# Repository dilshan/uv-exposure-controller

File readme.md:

## ATTiny2313 base electronic controller for UV exposure units.

*ATtiny2313A* MCU base exposure controller unit with two high-power relay driver stages, an audible notification unit, a safety lock, and a programmable timer. The programmable timer unit supports up to 999 seconds (approximately 16 minutes) of exposure.

This unit tests with four *NEC* 20W - 60cm (T8) black fluorescent tubes with four separate chokes and starter units.

The unit is specifically designed for developing screens (for screen-printing) and for paint curing.

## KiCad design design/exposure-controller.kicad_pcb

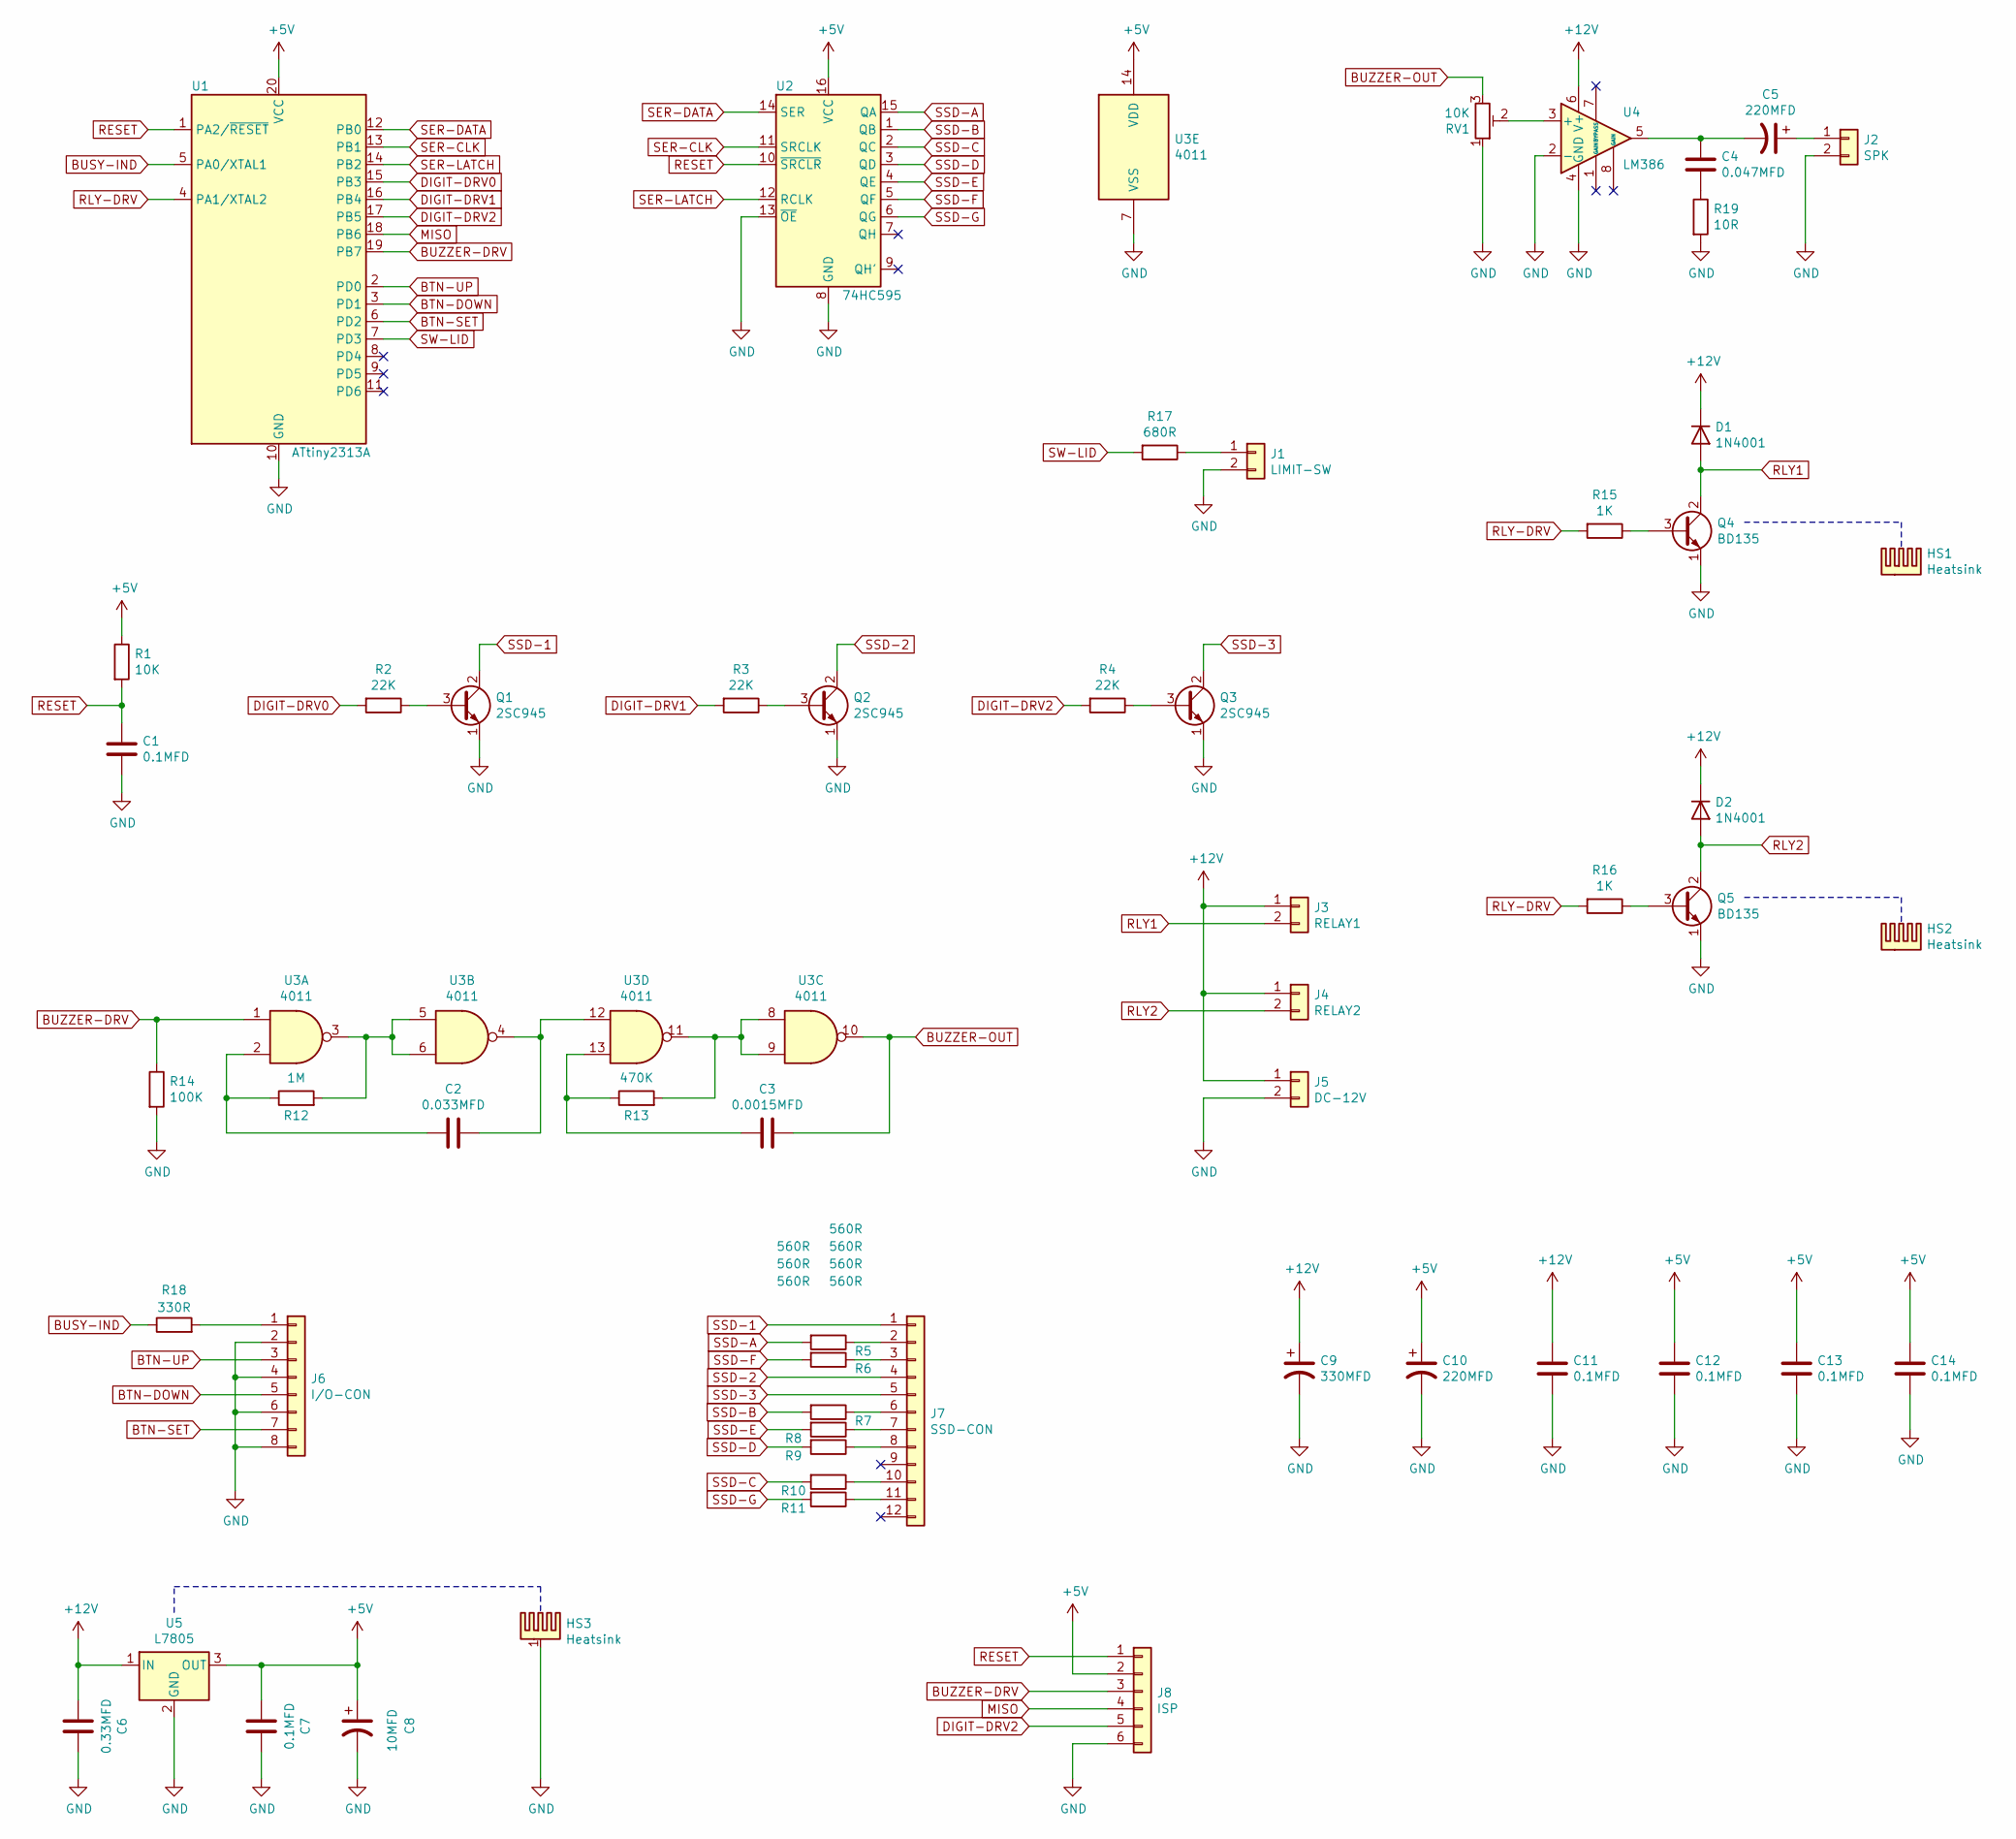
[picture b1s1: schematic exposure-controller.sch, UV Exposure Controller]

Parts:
C1, C7, C11, C12, C13, C14: 0.1MFD; C_Disc_D9.0mm_W5.0mm_P5.00mm
C2: 0.033MFD; C_Disc_D7.0mm_W2.5mm_P5.00mm
C3: 0.0015MFD; C_Disc_D4.7mm_W2.5mm_P5.00mm
C4: 0.047MFD; C_Disc_D7.0mm_W2.5mm_P5.00mm
C5, C10: 220MFD; CP_Radial_D8.0mm_P3.50mm
C6: 0.33MFD; C_Disc_D11.0mm_W5.0mm_P5.00mm
C8: 10MFD; CP_Radial_D5.0mm_P2.50mm
C9: 330MFD; CP_Radial_D8.0mm_P3.80mm
D1, D2: 1N4001; D_DO-41_SOD81_P10.16mm_Horizontal
HS1, HS2: Heatsink; Hetsink-21mm
HS3: Heatsink; Heatsink_Fischer_SK129-STS_42x25mm_2xDrill2.5mm
J1: LIMIT-SW; TerminalBlock_Phoenix_MKDS-1,5-2-5.08_1x02_P5.08mm_Horizont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
J2: SPK; TerminalBlock_Phoenix_MKDS-1,5-2-5.08_1x02_P5.08mm_Horizont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
J3: RELAY1; MENGFEI 8.5mm screw terminal - 2way
J4: RELAY2; MENGFEI 8.5mm screw terminal - 2way
J5: DC-12V; MENGFEI 8.5mm screw terminal - 2way
J6: I/O-CON; PinHeader_1x08_P2.54mm_Vertical
J7: SSD-CON; PinHeader_1x12_P2.54mm_Vertical
J8: ISP; PinHeader_1x06_P2.54mm_Vertical
Q1, Q2, Q3: 2SC945; TO-92L_Inline_Wide
Q4, Q5: BD135; TO-126-3_Vertical
R1: 10K; R_Axial_DIN0207_L6.3mm_D2.5mm_P10.16mm_Horizontal
R2, R3, R4: 22K; R_Axial_DIN0207_L6.3mm_D2.5mm_P10.16mm_Horizontal
R5, R6, R7, R8, R9, R10, R11: 560R; R_Axial_DIN0207_L6.3mm_D2.5mm_P10.16mm_Horizontal
R12: 1M; R_Axial_DIN0207_L6.3mm_D2.5mm_P10.16mm_Horizontal
R13: 470K; R_Axial_DIN0207_L6.3mm_D2.5mm_P10.16mm_Horizontal
R14: 100K; R_Axial_DIN0207_L6.3mm_D2.5mm_P10.16mm_Horizontal
R15, R16: 1K; R_Axial_DIN0207_L6.3mm_D2.5mm_P10.16mm_Horizontal
R17: 680R; R_Axial_DIN0207_L6.3mm_D2.5mm_P10.16mm_Horizontal
R18: 330R; R_Axial_DIN0207_L6.3mm_D2.5mm_P10.16mm_Horizontal
R19: 10R; R_Axial_DIN0207_L6.3mm_D2.5mm_P10.16mm_Horizontal
RV1: 10K; Potentiometer_Runtron_RM-065_Vertical
U1: ATtiny2313A; DIP-20_W7.62mm_LongPads
U2: 74HC595; DIP-16_W7.62mm_LongPads
U3: 4011; DIP-14_W7.62mm_LongPads
U4: LM386; DIP-8_W7.62mm_LongPads
U5: L7805; TO-220-3_Vertical

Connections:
+5V: C7.2, C8.1, C10.1, C12.1, C13.1, C14.1, J8.2, R1.1, U1.20 (VCC), U2.16 (VCC), U3.14 (VDD), U5.3 (OUT)
+12V: C6.2, C9.1, C11.1, D1.1 (K), D2.1 (K), J3.1, J4.1, J5.1, U4.6 (V+), U5.1 (IN)
BTN-DOWN: J6.5, U1.3 (PD1)
BTN-SET: J6.7, U1.6 (PD2)
BTN-UP: J6.3, U1.2 (PD0)
BUSY-IND: R18.1, U1.5 (PA0/XTAL1)
BUZZER-DRV: J8.3, R14.1, U1.19 (PB7), U3.1
BUZZER-OUT: C3.1, RV1.3, U3.10
DIGIT-DRV0: R2.2, U1.15 (PB3)
DIGIT-DRV1: R3.2, U1.16 (PB4)
DIGIT-DRV2: J8.5, R4.2, U1.17 (PB5)
GND: C1.2, C6.1, C7.1, C8.2, C9.2, C10.2, C11.2, C12.2, C13.2, C14.2, HS3.1, J1.2, J2.2, J5.2, J6.2, J6.4, J6.6, J6.8, J8.6, Q1.1 (E), Q2.1 (E), Q3.1 (E), Q4.1 (E), Q5.1 (E), R14.2, R19.2, RV1.1, U1.10 (GND), U2.8 (GND), U2.13 (~OE), U3.7 (VSS), U4.2 (-), U4.4 (GND), U5.2 (GND)
MISO: J8.4, U1.18 (PB6)
unnamed: C2.1, U3.4, U3.12
unnamed: C2.2, R12.1, U3.2
unnamed: C3.2, R13.1, U3.13
unnamed: C4.1, R19.1
unnamed: C4.2, C5.2, U4.5
unnamed: C5.1, J2.1
unnamed: J1.1, R17.1
unnamed: J6.1, R18.2
unnamed: J7.2, R5.1
unnamed: J7.3, R6.1
unnamed: J7.6, R7.1
unnamed: J7.7, R8.1
unnamed: J7.8, R9.1
unnamed: J7.10, R10.1
unnamed: J7.11, R11.1
unnamed: Q1.3 (B), R2.1
unnamed: Q2.3 (B), R3.1
unnamed: Q3.3 (B), R4.1
unnamed: Q4.3 (B), R15.1
unnamed: Q5.3 (B), R16.1
unnamed: R12.2, U3.3, U3.5, U3.6
unnamed: R13.2, U3.8, U3.9, U3.11
unnamed: RV1.2, U4.3 (+)
RESET: C1.1, J8.1, R1.2, U1.1 (PA2/~RESET), U2.10 (~SRCLR)
RLY1: D1.2 (A), J3.2, Q4.2 (C)
RLY2: D2.2 (A), J4.2, Q5.2 (C)
RLY-DRV: R15.2, R16.2, U1.4 (PA1/XTAL2)
SER-CLK: U1.13 (PB1), U2.11 (SRCLK)
SER-DATA: U1.12 (PB0), U2.14 (SER)
SER-LATCH: U1.14 (PB2), U2.12 (RCLK)
SSD-1: J7.1, Q1.2 (C)
SSD-2: J7.4, Q2.2 (C)
SSD-3: J7.5, Q3.2 (C)
SSD-A: R5.2, U2.15 (QA)
SSD-B: R7.2, U2.1 (QB)
SSD-C: R10.2, U2.2 (QC)
SSD-D: R9.2, U2.3 (QD)
SSD-E: R8.2, U2.4 (QE)
SSD-F: R6.2, U2.5 (QF)
SSD-G: R11.2, U2.6 (QG)
SW-LID: R17.2, U1.7 (PD3)

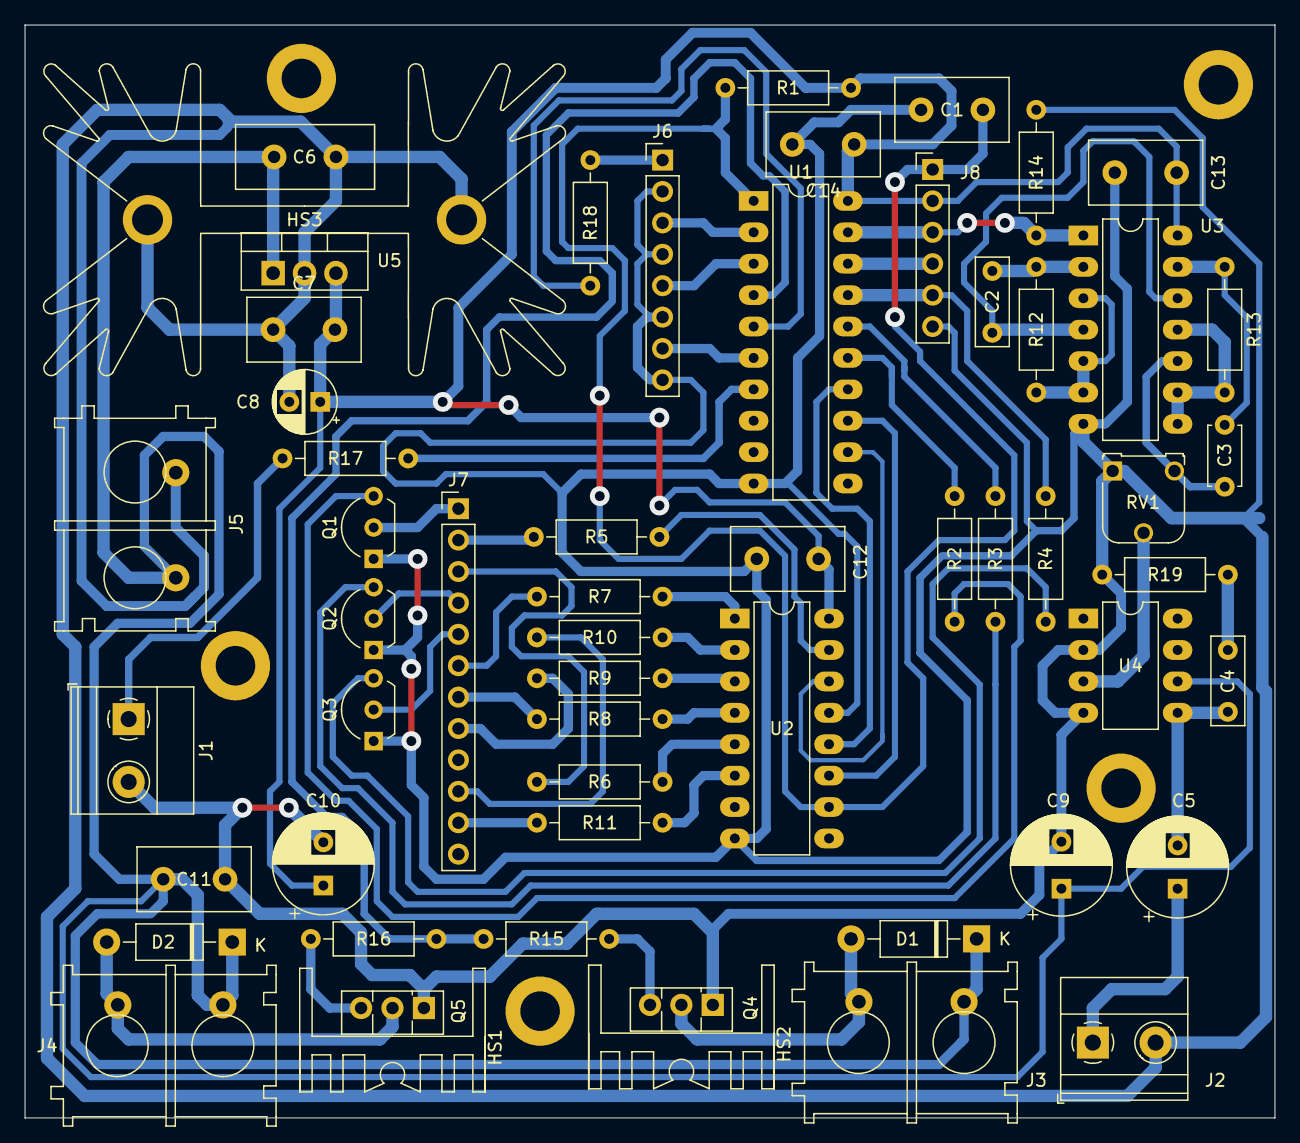
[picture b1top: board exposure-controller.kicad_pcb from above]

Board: 2 copper layers, 101.1 x 88.4 mm, 62 parts (0 on the bottom side), 54 nets.

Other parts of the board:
 : MountingHole_3.2mm_M3_DIN965_Pad
 #2,  #3,  #4,  #5: MountingHole_3.2mm_M3_DIN965_Pad

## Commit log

2021-02-20 Initial version of controller board design & ATtiny2313 firmware.
2021-02-20 Add 3D view of the controller PCB. :framed_picture:
2021-02-20 Add PDF version of the schematic.
2021-02-20 Add readme file and crop 3D image.
